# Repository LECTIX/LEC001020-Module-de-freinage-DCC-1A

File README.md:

# LEC001020-Module-de-freinage-DCC-1A
Fichiers sources pour le produit LEC001020

## Description du produit

Arrêtez et redémarrez vos convois de manière automatique et réaliste avec des arrêts et redémarrages progressifs des trains.
- **Technologie ABC**
- **Courrant maximum** de 1A.
- **Compatibilité DCC uniquement** (digital). Les décodeurs doivent être compatible avec la technologie ABC ([Cf. notice](docs/manual_fr.pdf)).

## Utiliser les fichiers sources pour fabriquer le produit

Il n'est **pas nécessaire de savoir souder ou d'être bon en électronique** pour se procurer ce produit. Grâce aux fichiers sources publiés ici, vous pouvez être en mesure de faire fabriquer ce produit par un sous traitant.

### Faire fabriquer chez un sous traitant

Il est aujourd'hui possible de faire fabriquer à moindre cout des cartes électroniques. Nous recommendons [JLCPCB](https://jlcpcb.com/) si vous voulez aller au moins cher. Si vous préférez un acteur européen, [eurocircuits](https://www.eurocircuits.com/) est un des acteurs reconnus.

1. Télécherger les sources de ce produit en cliquant sur le bouton `Code`, puis `Download ZIP`.
1. Décompresser le dossier.
1. Les fichiers pour la fabrication se trouvent dans le répertoire `hardware/prod`.
1. Se connecter sur [https://cart.jlcpcb.com/quote](https://cart.jlcpcb.com/quote)
1. Cliquer sur le bouton `Add gerber file` et sélectionner le fichier `gerbers.zip`.
1. Sélectionnez la quantité de cartes que vous souhaitez dans le champs `PCB Qty`.
1. Laisser toutes les autres options par défaut, puis cliquez sur le toggle switch en face de `PCB Assembly`, et enfin sur le bouton `confirm`.
1. Une preview de la carte électronique sans les composants doit apparaitre. Cliquez sur `NEXT`.
1. Cliquez sur le bouton `Add BOM File`, puis sélectionnez le fichier `bom.csv`
1. Cliquez sur le bouton `Add CPL File`, puis sélectionnez le fichier `pos.csv`
1. **Vérifier que tous les composants sont en stock** et bien sélectionnés, puis cliquez sur `NEXT`.
1. Une preview de la carte avec ses composants apparait. Continuer le chemin en cliquant sur `NEXT`.
1. Le prix final apparait. Sélectionnez la catégorie du produit, puis cliquez sur `SAVE TO CART`.
1. Une fois sauvegardé dans votre panier, vous pouvez valider votre commande et choisir le moyen d'acheminement. Afin de ne pas avoir à se préoccuper des frais de douane, nous vous conseillons de choisir une méthode d'expédition DDP.

Vous receverez vos cartes sous 1 à 3 semaines. 

**Nous ne sommes en aucun cas responsables des cartes qui arriveraient défectueuses ou non fonctionnelles.**

### Modifications des fichiers sources

Installez kicad 6 (ou version supérieure), et ouvrez le fichier LEC001020.kicad_pro

### Regénérer les fichiers gerber, BOM, et position (Optionnel)

Peut se faire simplement en utilisant kikit :

```
cd hardware
docker run --rm -w /kikit -v $PWD:/kikit yaqwsx/kikit kikit fab jlcpcb --assembly --no-drc --schematic LEC001020.kicad_sch --field LCSC --corrections JLCPCB_CORRECTION --nametemplate LEC001020_{} LEC001020.kicad_pcb prod/

```
## Notices
[Manuel FR](docs/manual_fr.pdf)

[Manuel EN](docs/manual_en.pdf)

## License
Tous nos fichiers sont plubliés sous la license CERN Open Hardware Licence Version 2 - Strongly Reciprocal

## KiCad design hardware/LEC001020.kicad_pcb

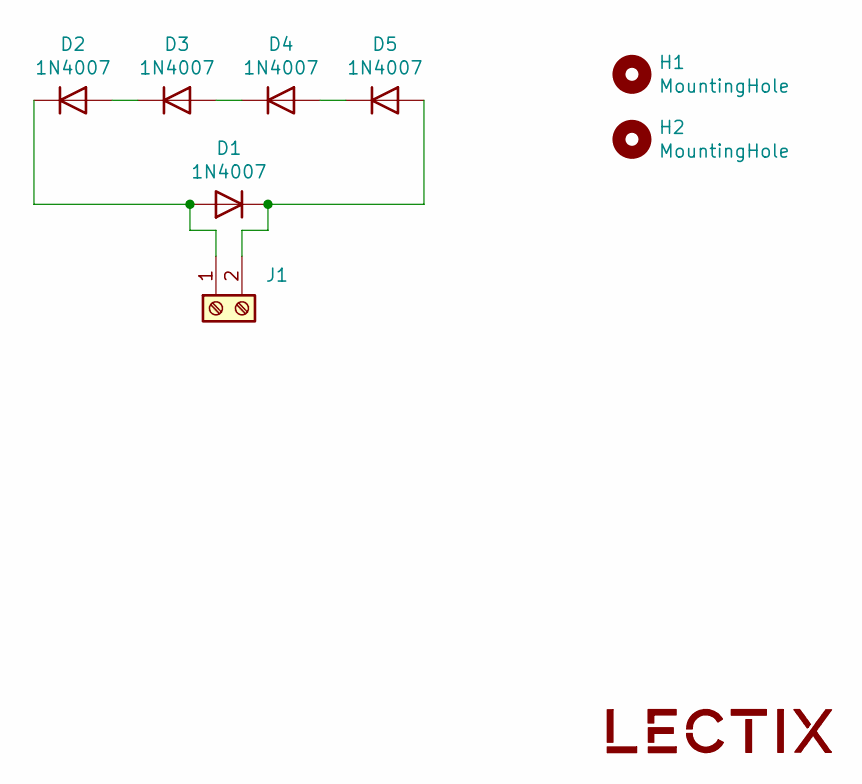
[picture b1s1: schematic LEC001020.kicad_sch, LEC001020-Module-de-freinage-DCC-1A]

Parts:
D1, D2, D3, D4, D5: 1N4007; D_SMA; LCSC C95872
H1, H2: MountingHole; MountingHole_3.2mm_M3
J1: Screw_Terminal_01x02_blue; TerminalBlock_bornier-2_P5.08mm-blue; MPN DB301V-5.0-2P-BU-P; LCSC C430621
LOGO1: logo_lectix_25mm; Logo_10mm

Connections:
unnamed: D1.1 (K), D5.2 (A), J1.2
unnamed: D1.2 (A), D2.1 (K), J1.1
unnamed: D2.2 (A), D3.1 (K)
unnamed: D3.2 (A), D4.1 (K)
unnamed: D4.2 (A), D5.1 (K)

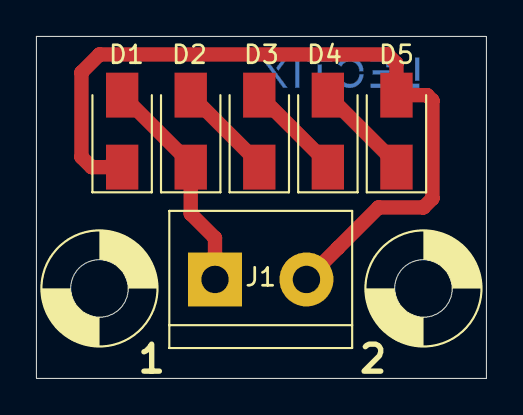
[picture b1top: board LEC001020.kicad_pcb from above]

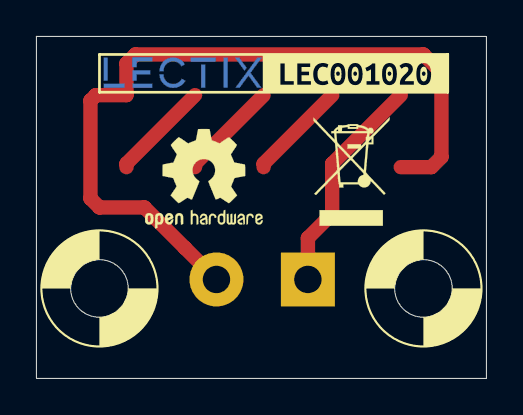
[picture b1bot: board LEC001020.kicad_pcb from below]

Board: 2 copper layers, 25.0 x 19.0 mm, 10 parts (2 on the bottom side), 5 nets.

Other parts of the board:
kibuzzard-62971ED3: G***; kibuzzard-62971ED3

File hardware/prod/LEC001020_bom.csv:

Comment,Designator,Footprint,LCSC
1N4007,"D1,D2,D3,D4,D5",Diode_SMD:D_SMA,C95872
Screw_Terminal_01x02_blue,J1,0_connectors:TerminalBlock_bornier-2_P5.08mm-blue,C430621
logo_lectix_25mm,LOGO1,0_logos:Logo_10mm,

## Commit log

2023-03-26 Add gitignore and License
2023-03-26 Add source files and README
2023-03-26 Update schematic sheet settings + add open hardware logo
2023-03-26 Add prod files
2023-03-26 Add product manuals
2023-03-26 Add pdf schematic file
2023-03-26 Add tuto video

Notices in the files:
hardware/LEC001020.kicad_sch:
CERN-OHL-S-2.0 license
